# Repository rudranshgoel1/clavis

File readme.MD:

# Clavis

### Why did I make it?
I have always did software, and I wanted to dip my hands in hardware, so my first project was actually a USB Hub, but I was too lazy to submit that project and ofcourse too lazy to do this also, but I need a keyboard badly, so I made it instead of spending money to buy one.

### What was the hardest part about this ?
First time trying hardware and its actually interesting, I lowkey ditched software so hard, I haven't touched anything for the past week or so.
Really fun doing hardware not gonna lie!

Features:

- RotaryEncoder for Volume Control
- 61 keys
- Raspberry Pi Pico
- Customised layout
- KMK firmware
- Clavis Branded PCB
- Custom case

### Schematic

### PCB 

### Case

- Side

I made some aesthetic for Clavis. Like I have added holes on all the sides to make it look more good

### 3D view of all parts 

link to full 3d thing-
https://cad.onshape.com/documents/4ed86aec979a191abbaea04f/w/0de3f3de07dd510f46e22fad/e/19a866b01119f1b2fa2c9c33?renderMode=0&uiState=69c921f1b2c317188620b060

A special thanks to Anay and Aditya who are helping me to make my projects better. Love them so much!

## BOM
|Name                                                         |Purpose                         |Quantity|Total Cost (USD)|Link                                                                             |Distributor    |
|-------------------------------------------------------------|--------------------------------|--------|----------------|---------------------------------------------------------------------------------|---------------|
|Akko Mirror Switch                                           |Switches for the keyboard       |61      |21.24           |https://stackskb.com/store/akko-mirror-switch-pack-of-45-pre-order/              |StacksKB       |
|Veekos Gradient Keycaps (Cherry Profile) (135 keys) (Blue)   |Keycaps for the keyboard        |1       |13.90           |https://stackskb.com/store/veekos-gradient-keycaps-cherry-profile-135-keys/      |StacksKB       |
|Durock Smokey Screw-In Stabilizers V2 (4+1 w/ 6.25u spacebar)|Stabilizers for longer keys     |1       |17.00           |https://stackskb.com/store/durock-smokey-screw-in-stabilizers-v2/                |StacksKB       |
|EC11 Rotary Encoder with Switch                              |RotaryEncoder for Volume Control|1       |0.68            |https://www.flyrobo.in/15mm-ec11-rotary-encoder-with-switch-digital-potentiometer|Fly Robo       |
|Diode 1N4148 Through - Hole                                  |Diode for every switch          |1       |1.08            |https://www.amazon.in/dp/B084ZP5BJ3?_encoding=UTF8&psc=1                         |Amazon         |
|Raspberry Pi Pico                                            |Rasp Pi Pico as the MCU         |1       |6.40            |https://www.amazon.in/Raspberry-Pi-Headers-Soldered-Micro/dp/B08WPNM7JB          |Amazon         |
|PCB                                                          |Main PCB of the keyboard        |5       |27.47           |https://jlcpcb.com/                                                              |JLPCB          |
|M3 x 8mm Bolt                                                |Screws                          |10      |1.73            |https://www.amazon.in/dp/B07X8PHXKB                                              |Amazon         |
|M3 Nuts                                                      |Screws                          |12      |0.79            |https://www.amazon.in/dp/B09J92WY5Q                                              |Amazon         |
|M3 x 5mm Heatset Insert                                      |Screws                          |25      |2.09            |https://www.amazon.in/dp/B0CX1BS7DJ                                              |Amazon         |
|Soldering Iron Kit                                           |Soldering Iron Kit              |1       |5.26            |https://www.amazon.in/dp/B0FC2YM1RY                                              |Amazon         |
|Case                                                         |Shipping - Case for the keyboard|1       |5.00            |                                                                                 |Printing Legion|

## Shipping
Amazon + StacksKB = ~$2
Printing Legion = ~$5

Total Shipping = $7

## Total Pricing
The total price comes out to be 9,166 INR ($97.64)
Total Shipping = $7

The pricing might slightly vary due to flash sales, and dollar market trends.

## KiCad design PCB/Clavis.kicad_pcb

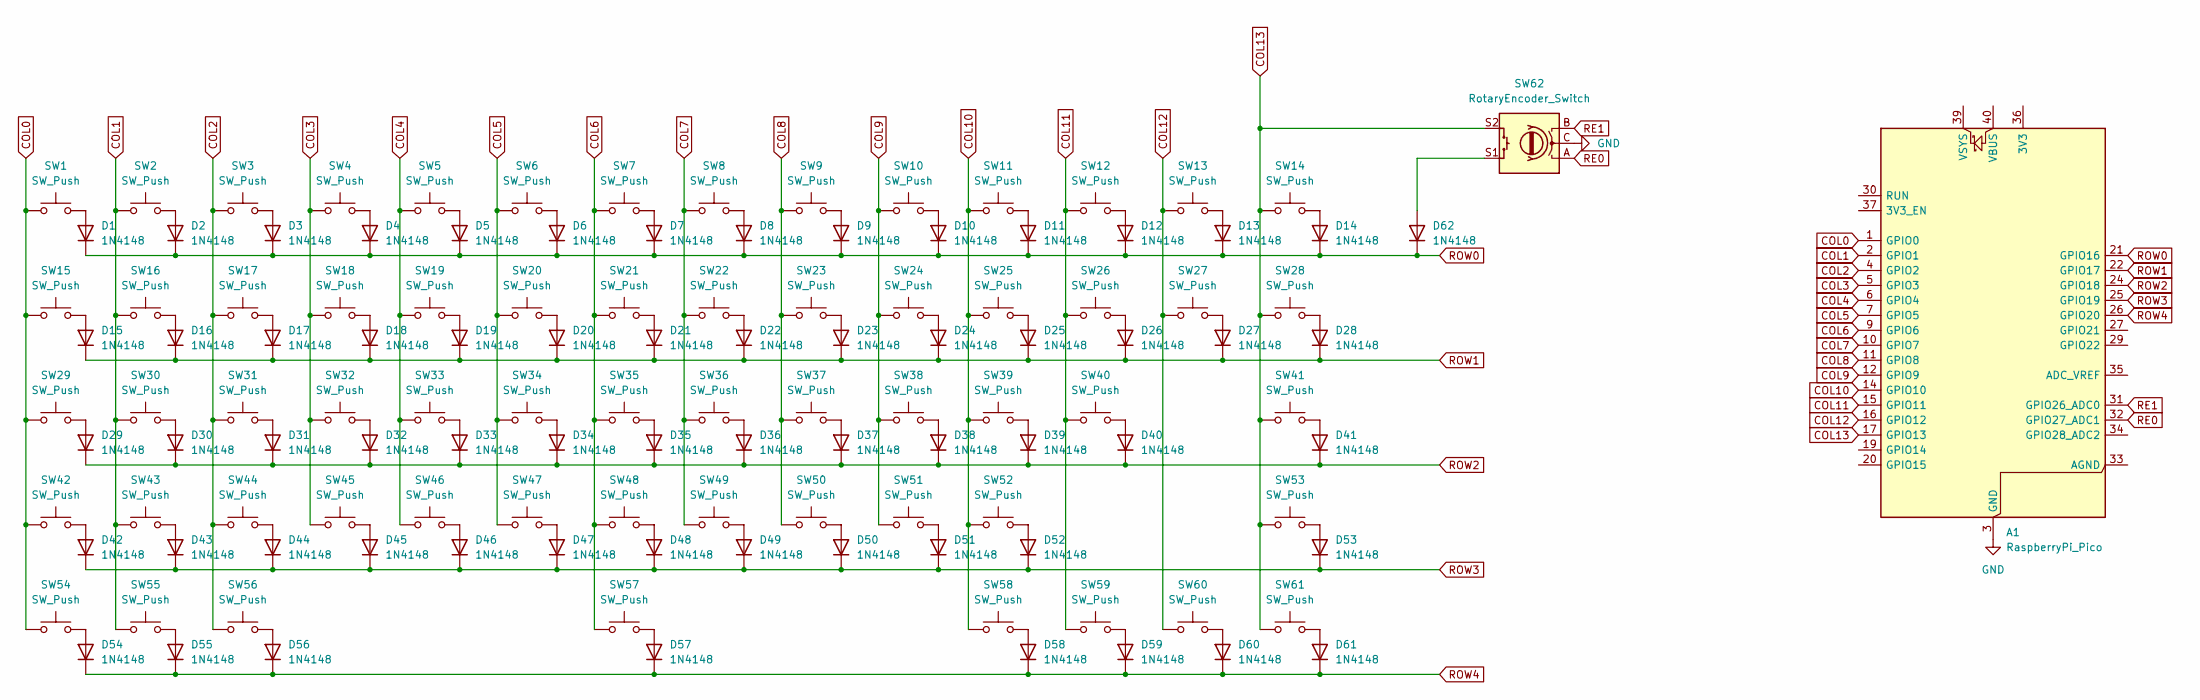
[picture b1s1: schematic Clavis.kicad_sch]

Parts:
A1: RaspberryPi_Pico; RaspberryPi_Pico_Common_THT
D1, D2, D3, D4, D5, D6, D7, D8, D9, D10, D11, D12, D13, D14, D15, D16, D17, D18, D19, D20, D21, D22, D23, D24, D25, D26, D27, D28, D29, D30, D31, D32, D33, D34, D35, D36, D37, D38, D39, D40, D41, D42, D43, D44, D45, D46, D47, D48, D49, D50, D51, D52, D53, D54, D55, D56, D57, D58, D59, D60, D61, D62: 1N4148; D_DO-35_SOD27_P7.62mm_Horizontal
SW1, SW2, SW3, SW4, SW5, SW6, SW7, SW8, SW9, SW10, SW11, SW12, SW13, SW16, SW17, SW18, SW19, SW20, SW21, SW22, SW23, SW24, SW25, SW26, SW27, SW30, SW31, SW32, SW33, SW34, SW35, SW36, SW37, SW38, SW39, SW40, SW43, SW44, SW45, SW46, SW47, SW48, SW49, SW50, SW51, SW52: SW_Push; SW_Cherry_MX_1.00u_PCB
SW14: SW_Push; SW_Cherry_MX_2.00u_PCB
SW15, SW28: SW_Push; SW_Cherry_MX_1.50u_PCB
SW29: SW_Push; SW_Cherry_MX_1.75u_PCB
SW41, SW42: SW_Push; SW_Cherry_MX_2.25u_PCB
SW53: SW_Push; SW_Cherry_MX_2.75u_PCB
SW54, SW55, SW56, SW58, SW59, SW60, SW61: SW_Push; SW_Cherry_MX_1.25u_PCB
SW57: SW_Push; SW_Cherry_MX_6.25u_PCB
SW62: RotaryEncoder_Switch; RotaryEncoder_Alps_EC11E-Switch_Vertical_H20mm

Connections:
COL0: A1.1 (GPIO0), SW1.1, SW15.1, SW29.1, SW42.1, SW54.1
COL1: A1.2 (GPIO1), SW2.1, SW16.1, SW30.1, SW43.1, SW55.1
COL2: A1.4 (GPIO2), SW3.1, SW17.1, SW31.1, SW44.1, SW56.1
COL3: A1.5 (GPIO3), SW4.1, SW18.1, SW32.1, SW45.1
COL4: A1.6 (GPIO4), SW5.1, SW19.1, SW33.1, SW46.1
COL5: A1.7 (GPIO5), SW6.1, SW20.1, SW34.1, SW47.1
COL6: A1.9 (GPIO6), SW7.1, SW21.1, SW35.1, SW48.1, SW57.1
COL7: A1.10 (GPIO7), SW8.1, SW22.1, SW36.1, SW49.1
COL8: A1.11 (GPIO8), SW9.1, SW23.1, SW37.1, SW50.1
COL9: A1.12 (GPIO9), SW10.1, SW24.1, SW38.1, SW51.1
COL10: A1.14 (GPIO10), SW11.1, SW25.1, SW39.1, SW52.1, SW58.1
COL11: A1.15 (GPIO11), SW12.1, SW26.1, SW40.1, SW59.1
COL12: A1.16 (GPIO12), SW13.1, SW27.1, SW60.1
COL13: A1.17 (GPIO13), SW14.1, SW28.1, SW41.1, SW53.1, SW61.1, SW62.S2
GND: A1.3 (GND), A1.8 (GND), A1.13 (GND), A1.18 (GND), A1.23 (GND), A1.28 (GND), A1.38 (GND), SW62.C
unnamed: D1.2 (A), SW1.2
unnamed: D2.2 (A), SW2.2
unnamed: D3.2 (A), SW3.2
unnamed: D4.2 (A), SW4.2
unnamed: D5.2 (A), SW5.2
unnamed: D6.2 (A), SW6.2
unnamed: D7.2 (A), SW7.2
unnamed: D8.2 (A), SW8.2
unnamed: D9.2 (A), SW9.2
unnamed: D10.2 (A), SW10.2
unnamed: D11.2 (A), SW11.2
unnamed: D12.2 (A), SW12.2
unnamed: D13.2 (A), SW13.2
unnamed: D14.2 (A), SW14.2
unnamed: D15.2 (A), SW15.2
unnamed: D16.2 (A), SW16.2
unnamed: D17.2 (A), SW17.2
unnamed: D18.2 (A), SW18.2
unnamed: D19.2 (A), SW19.2
unnamed: D20.2 (A), SW20.2
unnamed: D21.2 (A), SW21.2
unnamed: D22.2 (A), SW22.2
unnamed: D23.2 (A), SW23.2
unnamed: D24.2 (A), SW24.2
unnamed: D25.2 (A), SW25.2
unnamed: D26.2 (A), SW26.2
unnamed: D27.2 (A), SW27.2
unnamed: D28.2 (A), SW28.2
unnamed: D29.2 (A), SW29.2
unnamed: D30.2 (A), SW30.2
unnamed: D31.2 (A), SW31.2
unnamed: D32.2 (A), SW32.2
unnamed: D33.2 (A), SW33.2
unnamed: D34.2 (A), SW34.2
unnamed: D35.2 (A), SW35.2
unnamed: D36.2 (A), SW36.2
unnamed: D37.2 (A), SW37.2
unnamed: D38.2 (A), SW38.2
unnamed: D39.2 (A), SW39.2
unnamed: D40.2 (A), SW40.2
unnamed: D41.2 (A), SW41.2
unnamed: D42.2 (A), SW42.2
unnamed: D43.2 (A), SW43.2
unnamed: D44.2 (A), SW44.2
unnamed: D45.2 (A), SW45.2
unnamed: D46.2 (A), SW46.2
unnamed: D47.2 (A), SW47.2
unnamed: D48.2 (A), SW48.2
unnamed: D49.2 (A), SW49.2
unnamed: D50.2 (A), SW50.2
unnamed: D51.2 (A), SW51.2
unnamed: D52.2 (A), SW52.2
unnamed: D53.2 (A), SW53.2
unnamed: D54.2 (A), SW54.2
unnamed: D55.2 (A), SW55.2
unnamed: D56.2 (A), SW56.2
unnamed: D57.2 (A), SW57.2
unnamed: D58.2 (A), SW58.2
unnamed: D59.2 (A), SW59.2
unnamed: D60.2 (A), SW60.2
unnamed: D61.2 (A), SW61.2
unnamed: D62.2 (A), SW62.S1
RE0: A1.32 (GPIO27_ADC1), SW62.A
RE1: A1.31 (GPIO26_ADC0), SW62.B
ROW0: A1.21 (GPIO16), D1.1 (K), D2.1 (K), D3.1 (K), D4.1 (K), D5.1 (K), D6.1 (K), D7.1 (K), D8.1 (K), D9.1 (K), D10.1 (K), D11.1 (K), D12.1 (K), D13.1 (K), D14.1 (K), D62.1 (K)
ROW1: A1.22 (GPIO17), D15.1 (K), D16.1 (K), D17.1 (K), D18.1 (K), D19.1 (K), D20.1 (K), D21.1 (K), D22.1 (K), D23.1 (K), D24.1 (K), D25.1 (K), D26.1 (K), D27.1 (K), D28.1 (K)
ROW2: A1.24 (GPIO18), D29.1 (K), D30.1 (K), D31.1 (K), D32.1 (K), D33.1 (K), D34.1 (K), D35.1 (K), D36.1 (K), D37.1 (K), D38.1 (K), D39.1 (K), D40.1 (K), D41.1 (K)
ROW3: A1.25 (GPIO19), D42.1 (K), D43.1 (K), D44.1 (K), D45.1 (K), D46.1 (K), D47.1 (K), D48.1 (K), D49.1 (K), D50.1 (K), D51.1 (K), D52.1 (K), D53.1 (K)
ROW4: A1.26 (GPIO20), D54.1 (K), D55.1 (K), D56.1 (K), D57.1 (K), D58.1 (K), D59.1 (K), D60.1 (K), D61.1 (K)

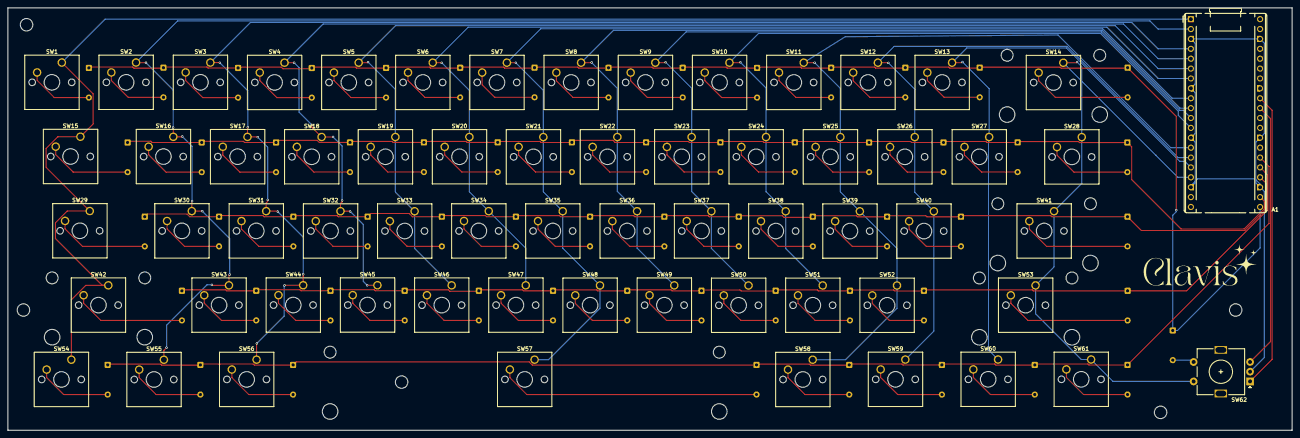
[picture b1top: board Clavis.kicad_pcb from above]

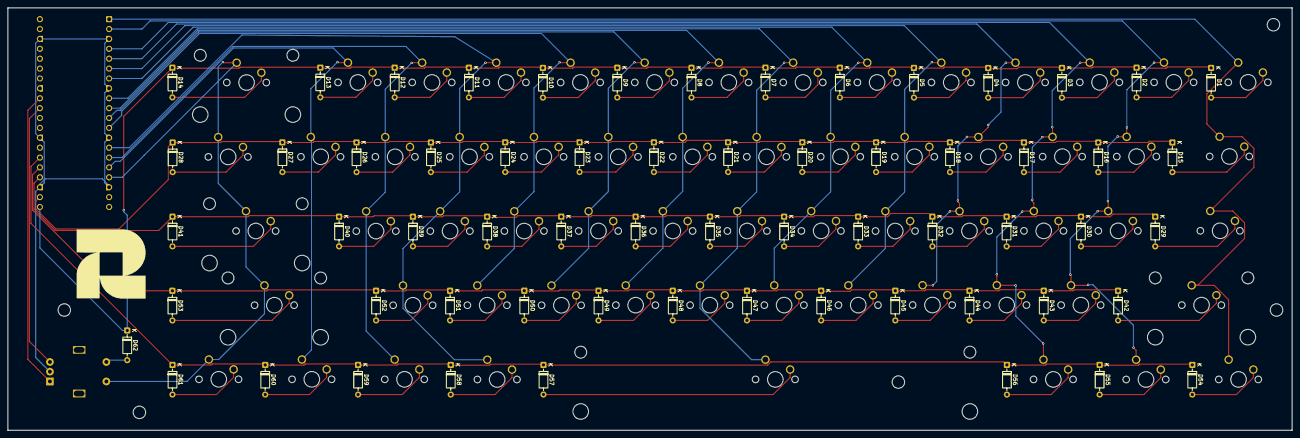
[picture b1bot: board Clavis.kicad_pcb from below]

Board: 2 copper layers, 330.0 x 108.5 mm, 125 parts (62 on the bottom side), 84 nets.

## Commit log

2026-03-26 main commit
2026-03-26 changed a few things
2026-03-29 made some changes
2026-03-29 readme
2026-03-31 Add STEP via LFS (fixed)
2026-03-31 cad files
